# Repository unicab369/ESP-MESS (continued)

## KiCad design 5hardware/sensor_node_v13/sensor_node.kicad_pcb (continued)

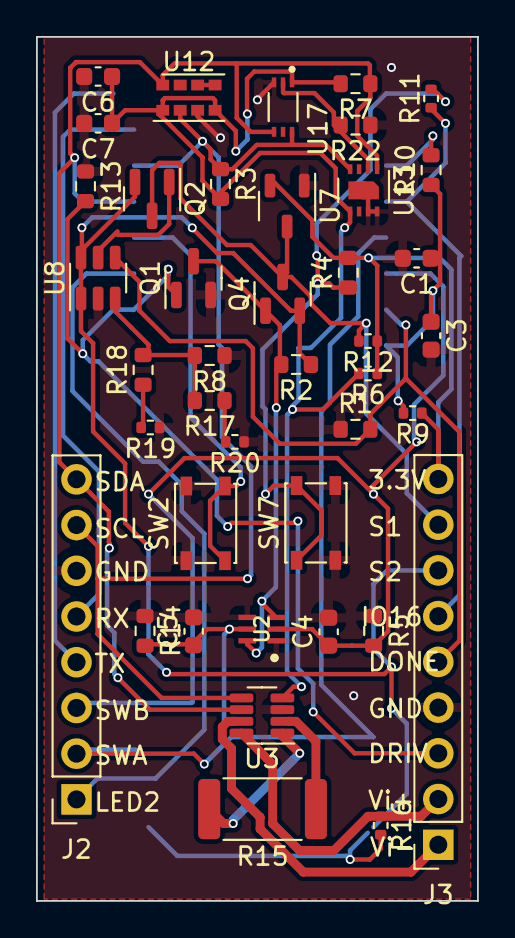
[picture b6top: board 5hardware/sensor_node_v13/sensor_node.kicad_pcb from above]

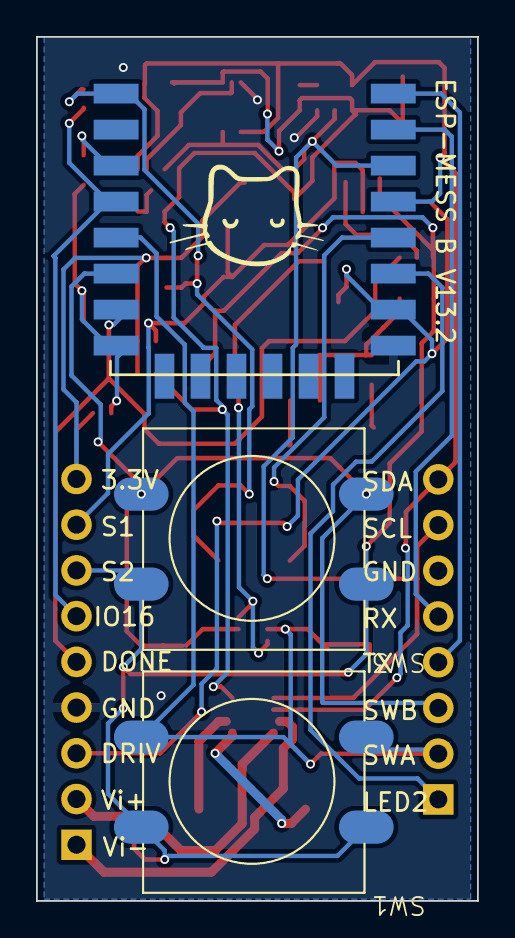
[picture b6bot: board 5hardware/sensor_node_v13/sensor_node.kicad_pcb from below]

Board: 2 copper layers, 24.5 x 48.0 mm, 44 parts (3 on the bottom side), 30 nets.

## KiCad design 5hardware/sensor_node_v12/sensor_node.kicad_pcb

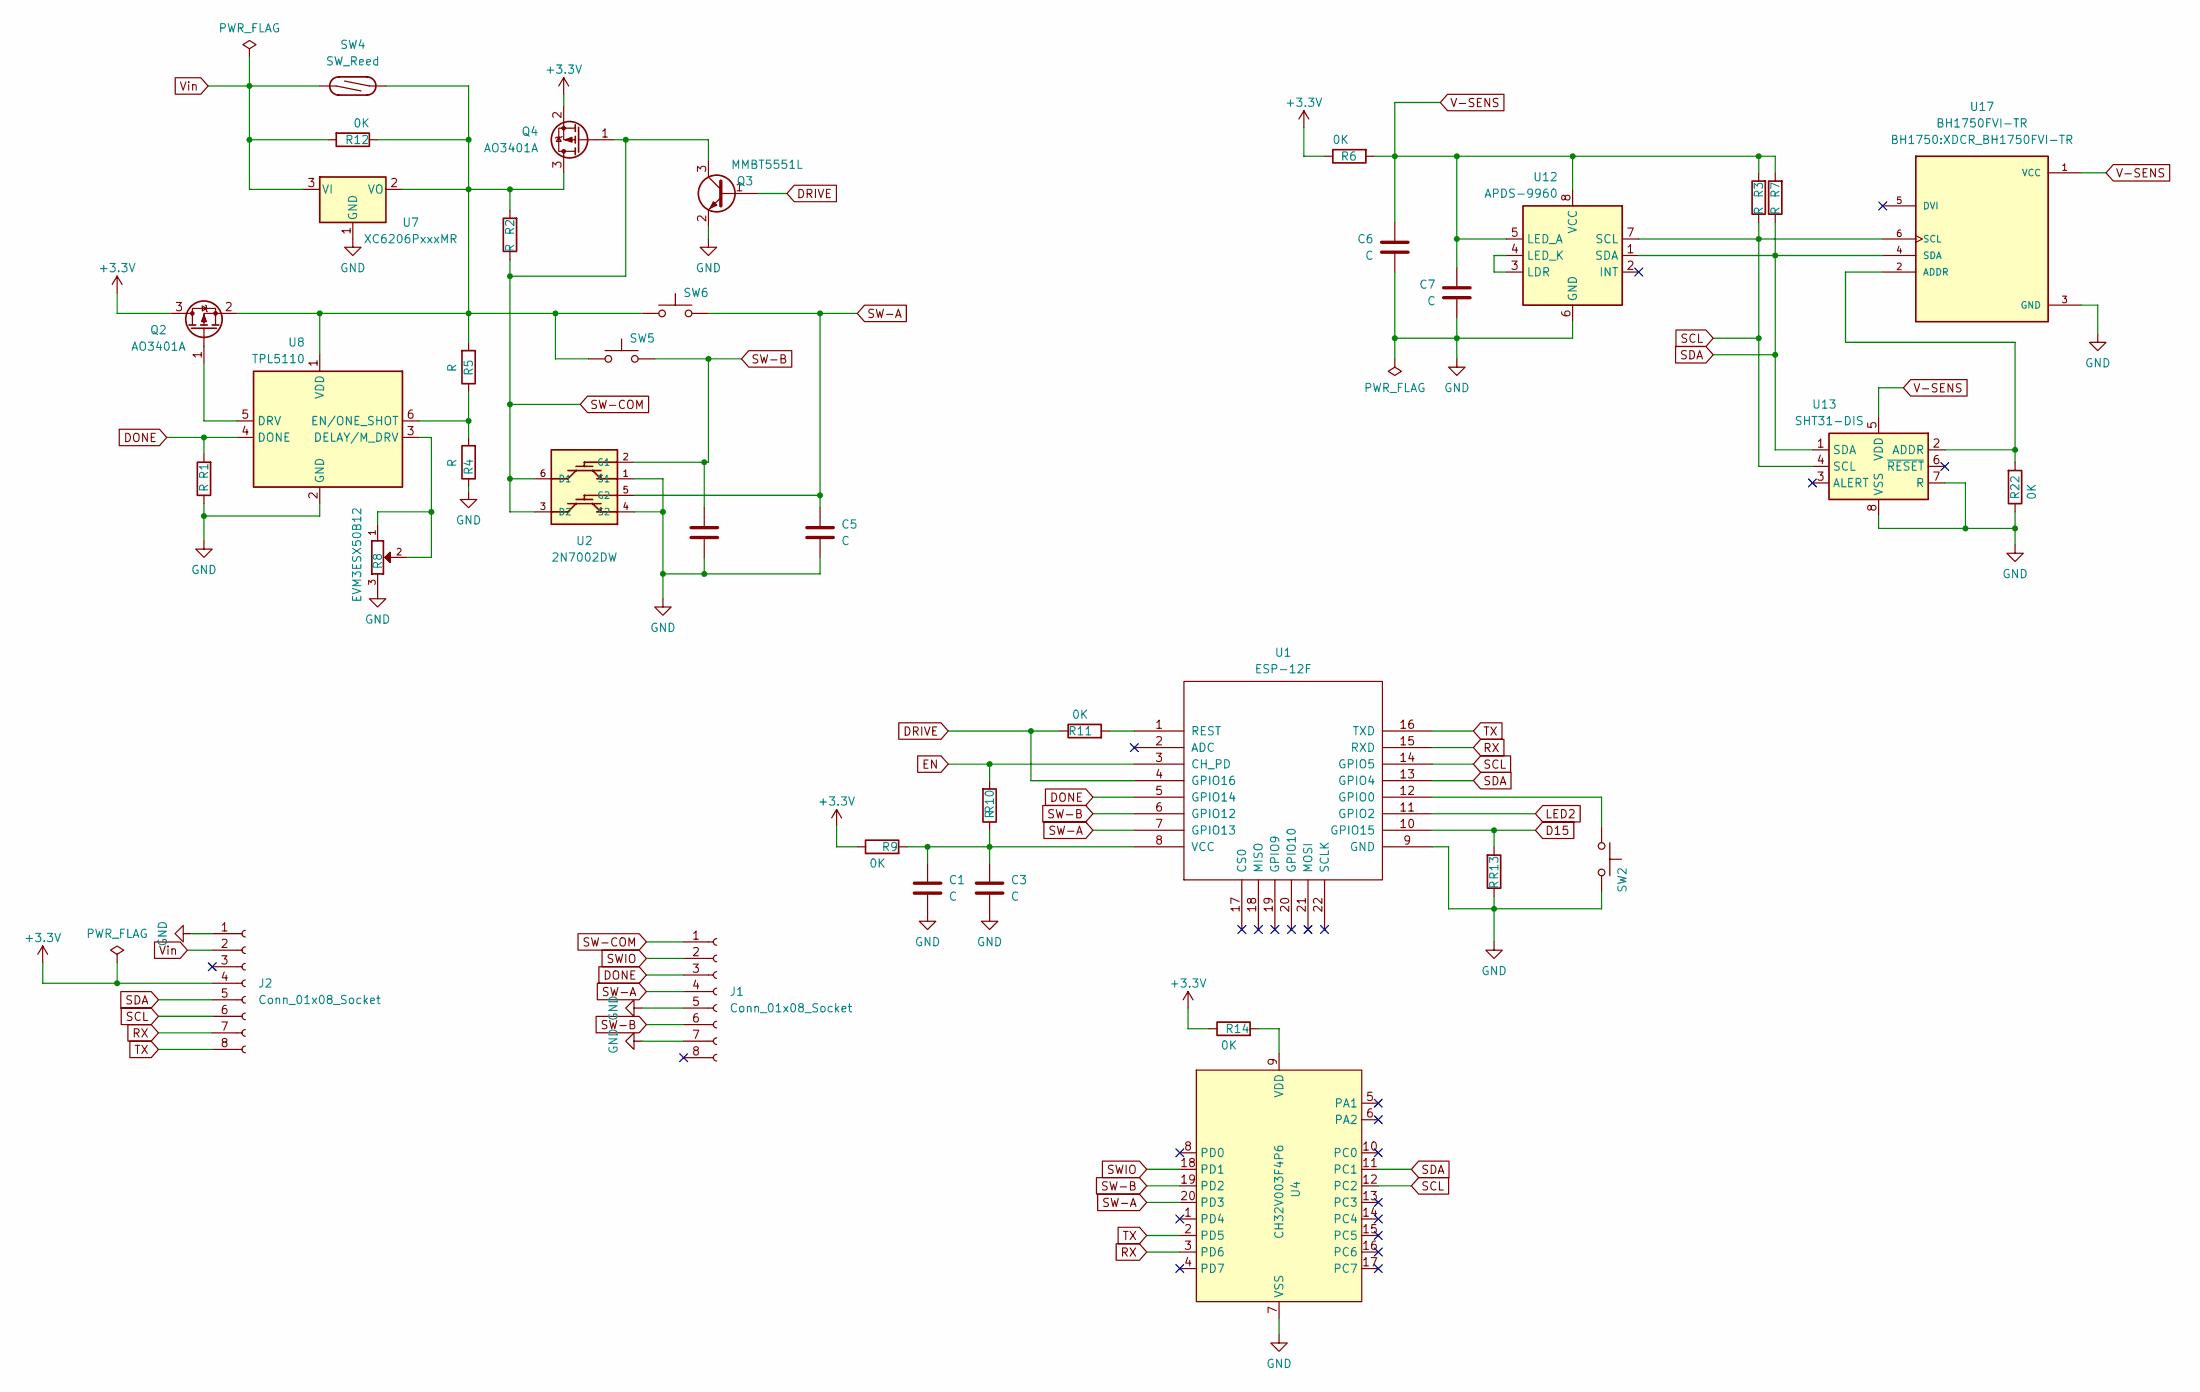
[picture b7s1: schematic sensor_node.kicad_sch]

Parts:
C1, C3, C4, C5, C6, C7: C; C_0603_1608Metric
J1, J2: Conn_01x08_Socket; PinSocket_1x08_P2.54mm_Vertical
Q2, Q4: AO3401A; SOT-23
Q3: MMBT5551L; SOT-23
R1, R2, R3, R4, R5, R7, R10, R13: R; R_0603_1608Metric
R6, R9, R11, R12, R14, R22: 0K; R_0603_1608Metric
R8: EVM3ESX50B12; EMV3ESX50B12
SW2, SW5, SW6: SW_Push; SW_SPST_PTS810
SW4: SW_Reed; SW_SPST_REED_CT10-XXXX-G1
U1: ESP-12F; ESP12_SMD
U2: 2N7002DW; SOT363
U4: CH32V003F4P6; TSSOP-20_4.4x6.5mm_P0.65mm
U7: XC6206PxxxMR; SOT-23-3
U8: TPL5110; SOT-23-6
U12: APDS-9960; Avago_APDS-9960
U13: SHT31-DIS; Sensirion_DFN-8-1EP_2.5x2.5mm_P0.5mm_EP1.1x1.7mm
U17: BH1750FVI-TR; XDCR_BH1750FVI-TR; PARTREV D

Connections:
+3.3V: J2.4, Q2.3 (D), Q4.2 (S), R6.1, R9.1, R14.1
D15: R13.2, U1.10 (GPIO15)
DONE: J1.3, R1.2, U1.5 (GPIO14), U8.4 (DONE)
DRIVE: Q3.1 (B), R11.1, U1.4 (GPIO16)
EN: R10.2, U1.3 (CH_PD)
GND: C1.2, C3.2, C4.2, C5.2, C6.2, C7.2, J1.5, J1.7, J2.1, Q3.2 (E), R1.1, R4.1, R8.3, R13.1, R22.1, SW2.1, U1.9 (GND), U2.1 (S1), U2.4 (S2), U4.7 (VSS), U7.1 (GND), U8.2 (GND), U12.6 (GND), U13.7 (R), U13.8 (VSS), U13.9 (VSS), U17.3 (GND)
LED2: U1.11 (GPIO2)
unnamed: Q2.1 (G), U8.5 (DRV)
unnamed: Q2.2 (S), Q4.3 (D), R2.2, R5.2, R12.1, SW4.1, SW5.2, SW6.2, U7.2 (VO), U8.1 (VDD)
unnamed: SW2.2, U1.12 (GPIO0)
unnamed: R11.2, U1.1 (REST)
unnamed: C1.1, C3.1, R9.2, R10.1, U1.8 (VCC)
unnamed: R14.2, U4.9 (VDD)
unnamed: R8.1, R8.2, U8.3 (DELAY/M_DRV)
unnamed: R4.2, R5.1, U8.6 (EN/ONE_SHOT)
unnamed: U12.3 (LDR), U12.4 (LED_K)
unnamed: R22.2, U13.2 (ADDR), U17.2 (ADDR)
RX: J2.7, U1.15 (RXD), U4.3 (PD6)
SCL: J2.6, R3.1, U1.14 (GPIO5), U4.12 (PC2), U12.7 (SCL), U13.4 (SCL), U17.6 (SCL)
SDA: J2.5, R7.1, U1.13 (GPIO4), U4.11 (PC1), U12.1 (SDA), U13.1 (SDA), U17.4 (SDA)
SW-A: C5.1, J1.4, SW6.1, U1.7 (GPIO13), U2.5 (G2), U4.20 (PD3)
SW-B: C4.1, J1.6, SW5.1, U1.6 (GPIO12), U2.2 (G1), U4.19 (PD2)
SW-COM: J1.1, Q3.3 (C), Q4.1 (G), R2.1, U2.3 (D2), U2.6 (D1)
SWIO: J1.2, U4.18 (PD1)
TX: J2.8, U1.16 (TXD), U4.2 (PD5)
V-SENS: C6.1, C7.1, R3.2, R6.2, R7.2, U12.5 (LED_A), U12.8 (VCC), U13.5 (VDD), U17.1 (VCC)
Vin: J2.2, R12.2, SW4.2, U7.3 (VI)

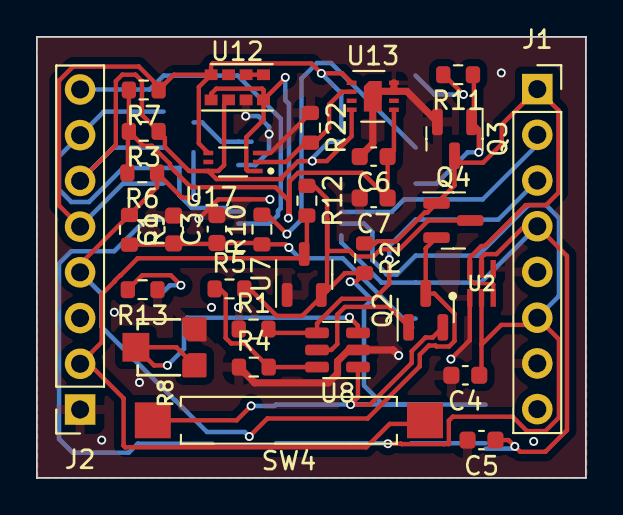
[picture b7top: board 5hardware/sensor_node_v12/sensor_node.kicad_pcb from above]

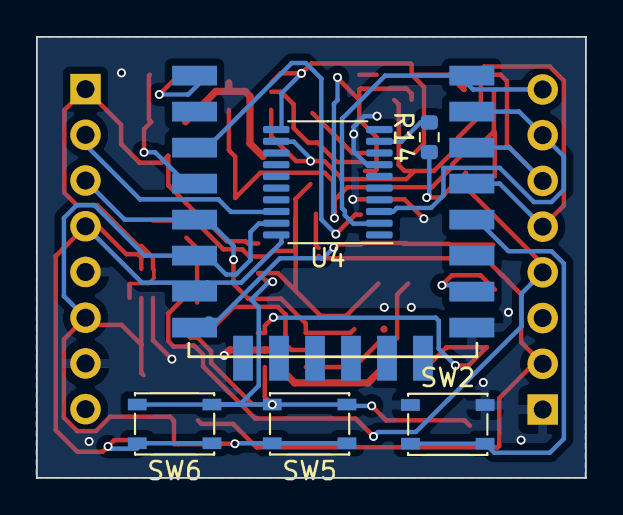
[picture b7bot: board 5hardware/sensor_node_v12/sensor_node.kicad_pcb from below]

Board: 2 copper layers, 30.5 x 24.5 mm, 38 parts (6 on the bottom side), 26 nets.

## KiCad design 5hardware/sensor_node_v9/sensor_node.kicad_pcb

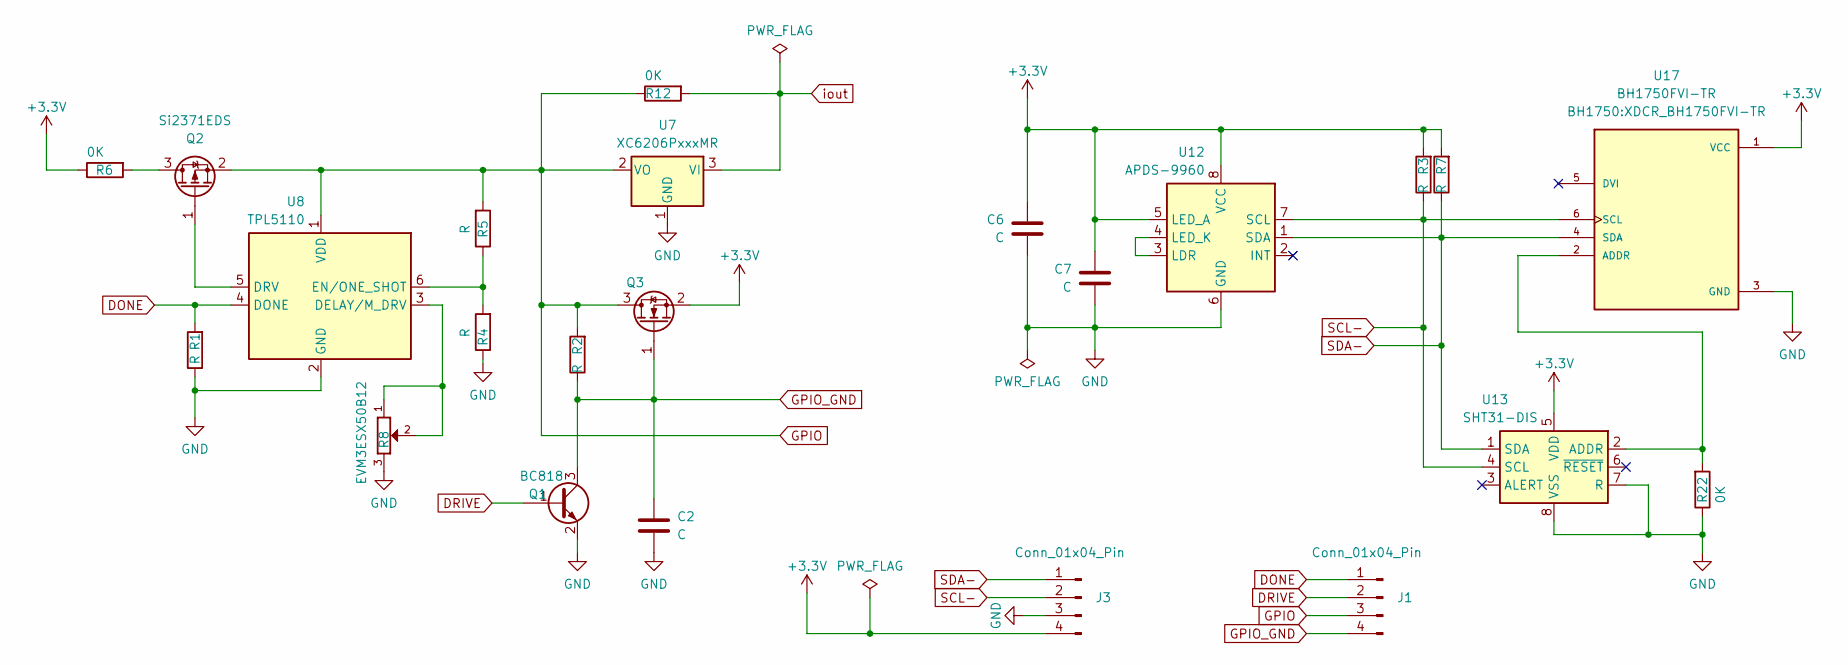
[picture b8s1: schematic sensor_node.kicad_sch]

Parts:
C2, C6, C7: C; C_0603_1608Metric
J1, J3: Conn_01x04_Pin; PinSocket_1x04_P2.54mm_Vertical
Q1: BC818; SOT-23
Q2: Si2371EDS; SOT-23
Q3: AO3400A; SOT-23
R1, R2, R3, R4, R5, R7: R; R_0603_1608Metric
R6, R12, R22: 0K; R_0603_1608Metric
R8: EVM3ESX50B12; EMV3ESX50B12
U7: XC6206PxxxMR; SOT-23-3
U8: TPL5110; SOT-23-6
U12: APDS-9960; Avago_APDS-9960
U13: SHT31-DIS; Sensirion_DFN-8-1EP_2.5x2.5mm_P0.5mm_EP1.1x1.7mm
U17: BH1750FVI-TR; XDCR_BH1750FVI-TR; PARTREV D

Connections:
+3.3V: C6.1, C7.1, J3.4, Q3.2 (S), R3.2, R6.1, R7.2, U12.5 (LED_A), U12.8 (VCC), U13.5 (VDD), U17.1 (VCC)
DONE: J1.1, R1.2, U8.4 (DONE)
DRIVE: J1.2, Q1.1 (B)
GND: C2.2, C6.2, C7.2, J3.3, Q1.2 (E), R1.1, R4.1, R8.3, R22.1, U7.1 (GND), U8.2 (GND), U12.6 (GND), U13.7 (R), U13.8 (VSS), U13.9 (VSS), U17.3 (GND)
GPIO: J1.3, Q2.2 (S), Q3.3 (D), R2.2, R5.2, R12.1, U7.2 (VO), U8.1 (VDD)
GPIO_GND: C2.1, J1.4, Q1.3 (C), Q3.1 (G), R2.1
unnamed: Q2.3 (D), R6.2
unnamed: Q2.1 (G), U8.5 (DRV)
unnamed: R8.1, R8.2, U8.3 (DELAY/M_DRV)
unnamed: R4.2, R5.1, U8.6 (EN/ONE_SHOT)
unnamed: U12.3 (LDR), U12.4 (LED_K)
unnamed: R22.2, U13.2 (ADDR), U17.2 (ADDR)
SCL-: J3.2, R3.1, U12.7 (SCL), U13.4 (SCL), U17.6 (SCL)
SDA-: J3.1, R7.1, U12.1 (SDA), U13.1 (SDA), U17.4 (SDA)
iout: R12.2, U7.3 (VI)

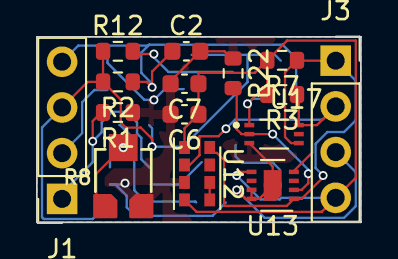
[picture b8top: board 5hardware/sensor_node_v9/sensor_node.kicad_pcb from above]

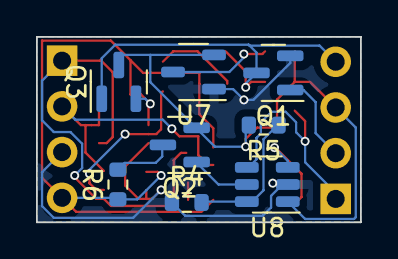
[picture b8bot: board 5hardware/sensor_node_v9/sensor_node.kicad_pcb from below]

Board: 2 copper layers, 18.0 x 10.3 mm, 23 parts (8 on the bottom side), 15 nets.

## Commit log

2023-10-10 migrate repo.
2023-10-10 fix issue with resetCount.
2023-10-10 added pcb designs. added docker files. addes scripts.
2023-10-10 update serv_device.
2023-10-10 removed Mng_Device.
2023-10-10 added DevConfigs.
2023-10-11 update PinSequence.
2023-10-11 update pulses.
2023-10-12 update printLog. Update storeBehavior.
2023-10-12 did some works.
2023-10-12 debug servo.
2023-10-12 debugging PCA96.
2023-10-12 separate Javascript file.
2023-10-12 update web components.
2023-10-12 update webServer. update behavior objects.
2023-10-12 update Storage tabSpace.
2023-10-12 update storage objects name.
2023-10-13 working behavior model.
2023-10-13 cleanup.
2023-10-13 separate Sto_Behavior.
2023-10-13 update Sto_Behavior. added Sto_Peer.
2023-10-13 working on Peer management.
2023-10-14 debug addPeer.
2023-10-14 debug EEPROM storage.
2023-10-14 update storage.
2023-10-14 udpate resetCounter.
2023-10-14 updating console input.
2023-10-14 update console input.
2023-10-15 added EEPROM_Extractor.
2023-10-15 debugging Sto_Peer.
2023-10-15 update peer storage.
2023-10-15 update Sto_Peer.
2023-10-16 adding web page.
2023-10-16 added more web pages.
2023-10-16 update webpage.
2023-10-16 update UI.
2023-10-16 update webServer.
2023-10-17 update web files.
2023-10-17 reorganize files.
2023-10-17 handle response.
2023-10-17 Added XT_DAC_Audio.
2023-10-17 separate scripts.
2023-10-17 update DevConf.
2023-10-17 update WebConfig page.
2023-10-18 working servo driver.
2023-10-18 update callbacks.
2023-10-18 refactor IOs.
2023-10-18 update pin sequence.
2023-10-19 added Serv_IO.
2023-10-19 working ControlOutput.
2023-10-21 updating schematic.
2023-10-22 updating ESP-Mess baseboard schematic for version 3.0
2023-10-22 updated schematic.
2023-10-22 schematic draft.
2023-10-23 label pins.
2023-10-23 added pcb design.
2023-10-23 updating pcb design.
2023-10-24 updated schematic. ESP32-C3 support.
2023-10-24 update pcb wirings.
2023-10-24 update pcb design.
2023-10-24 update pcb.
2023-10-24 Complete design phase1.
2023-10-25 update README.
2023-10-26 fixing wiring.
2023-10-26 fixing pcb design.
2023-10-26 updating pcb.
2023-10-26 fiixing connections.
2023-10-26 completed schematic.
2023-10-26 updated.
2023-10-27 working BLE and Bluetooth examples.
2023-10-28 working ESP32-C2 BLE.
2023-11-03 update schematic.
2023-11-03 working servo.
2023-11-04 update for ESP8266.
2023-11-05 added test for ESP-Now.
2023-11-05 update for ESP32.
2023-11-07 sensors readings cleanup. working ESP-Now between ESP8266 and ESP32.
2023-11-07 working sending data Records over ESP-Now.
2023-11-08 Post to iotPlotter.
2023-11-09 update Docs.
2023-11-10 added BLE Support.
2023-11-11 fixing crashes.
2023-11-11 debug crashes.
2023-11-11 fixed I2C sensors issue.
2023-11-12 debugging crashes.
2023-11-13 WORKING: ESP32 to ch32v Aurt Communication.
2023-11-14 FIXED: null pointer device.
2023-11-14 FIXED: storage bugs.
2023-11-14 WORKING: iotPlotter config.
2023-11-16 added test results for new BLE modules.
2023-11-17 Added RTC and AS5600.
2023-11-18 update paths.
2023-11-20 added uPlot.
2023-11-20 attempt to move ch32vfun base into the project.
2023-11-20 enable self logging.
2023-11-21 update BLE.
2023-11-21 added new binary.
2023-11-21 test Commit 1.
2023-11-22 graphData
2023-11-22 added GPS Mod.
2023-11-25 TEST: Epaper display.
2023-11-25 update uPlot.
2023-11-25 cleaning up.
2023-11-25 update plots.
2023-11-26 leaflet Map
2023-11-26 leaflet Map update folder structure, directory, and naming
2023-11-26 remove leaflet dist, using CDN instead
2023-11-26 testing i2C.
2023-11-26 test1
2023-11-28 added test code.
2023-11-28 added polygons.
2023-11-28 add dots.
2023-11-28 added i2c scanning.
2023-11-28 added ZoneLayout.
2023-11-30 draw, save and load zones using geoJson
2023-11-30 update loadGeoJSON button
2023-11-30 i2C update.
2023-12-02 added ESP32-S3
2023-12-02 remove a file
2023-12-02 update SaveZoneGeoJSON error
2023-12-03 added sensors tests.
2023-12-04 Added README for new BLE modules.
2023-12-04 Added test result for Ebyte BT07.
2023-12-04 update PageMap.
2023-12-04 renamed file.
2023-12-05 WORKING: V2 Board. Fix command issues.
2023-12-06 WORKING: V3 Board new pins updates.
2023-12-08 update ios.
2023-12-11 ESP32-C3 update.
2023-12-12 debugging BLE.
2023-12-12 WORKING: BLE with CH32v.
2023-12-13 BLE update.
2023-12-13 fixed bug.
2023-12-16 added JDY-27 info.
2023-12-17 added Network Topology definitions.
2023-12-17 added spaces.
2023-12-20 added INA219. Still Debugging.
2023-12-20 WORKING: Receive sensors readings via xSerial.
2023-12-22 update folder and file layout
2023-12-24 update SensorNode V4.0 schematic.
2024-01-01 WORKING: displays tests.
2024-01-02 panelized PCBs.
2024-01-04 WORKING: Receive sensors data. Check Sd card.
2024-01-20 debugging.
2024-01-20 working BLE connection.
2024-01-21 fixed BLE crash.
2024-01-23 update doc.
2024-01-24 WORKING: ESP8266 EspNow Sensor.
2024-02-01 update project structure. added ESP-Mess baseboard V7.0.
2024-02-03 added logo.
2024-02-03 added testpoints.
2024-02-10 Preact app
2024-02-14 added INA219 and INA226 test.
2024-02-14 added Webserver Test.
2024-02-15 fixed storage crash. upate ESPNow.
2024-02-15 added device interface.
2024-02-17 update EspNow sensor.
2024-02-17 update storage variables.
2024-02-20 updated Sto_Behavior.
2024-02-20 added PlotterQueue.
2024-02-20 cleanup. update platfromio.ini.
2024-02-21 refactoring.
2024-02-22 update queue.
2024-02-27 update button trigger.
2024-03-01 updated PCB.
2024-03-01 ESP8266 crash fix.
2024-03-01 remove interrupts.
2024-03-21 update i2c sensor.
2024-03-22 update sensors.
2024-03-23 update ina219.
2024-03-24 update sensor.
2024-03-24 schematic upate.
2024-03-25 adjust sensor reading time.
2024-03-25 cleanup,.
2024-04-02 update PCBs.
2024-04-02 udpate PCBs.
